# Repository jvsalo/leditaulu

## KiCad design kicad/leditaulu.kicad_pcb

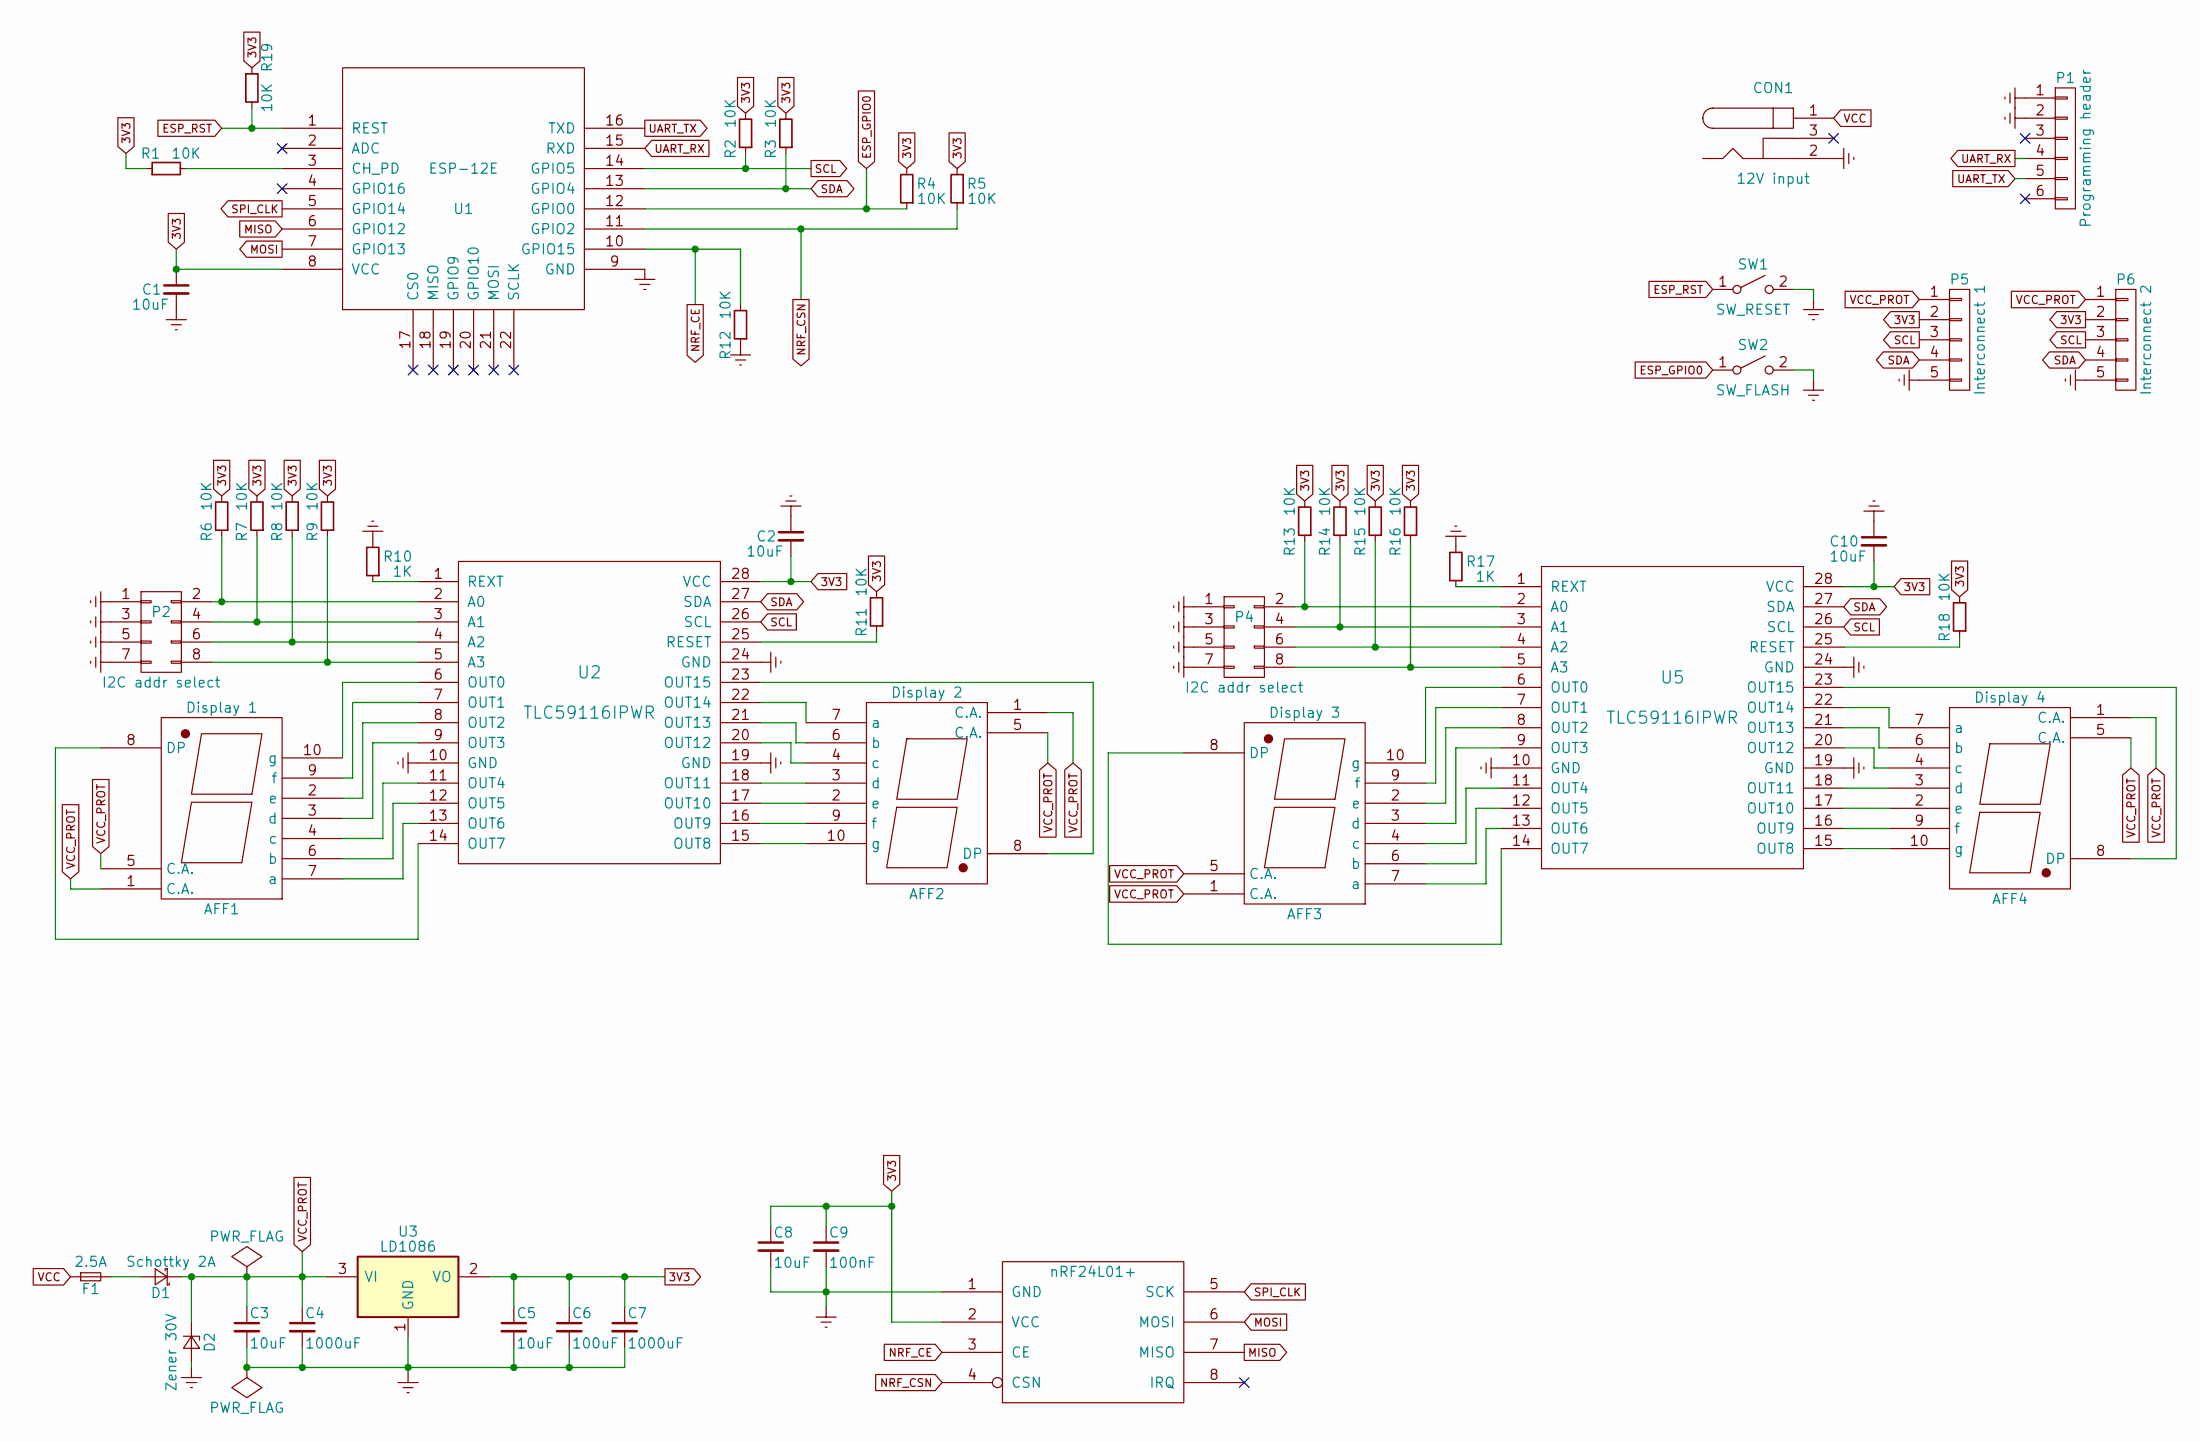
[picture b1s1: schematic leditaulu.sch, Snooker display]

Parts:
AFF1: Display 1; IDC_Header_Straight_10pins
AFF2: Display 2; IDC_Header_Straight_10pins
AFF3: Display 3; IDC_Header_Straight_10pins
AFF4: Display 4; IDC_Header_Straight_10pins
C1, C2, C3, C5, C8, C10: 10uF; C_1206_HandSoldering
C4, C7: 1000uF; CP_Radial_D10.0mm_P5.00mm
C6: 100uF; C_1206_HandSoldering
C9: 100nF; C_1206_HandSoldering
CON1: 12V input; BARREL_JACK
D1: Schottky 2A; D_SOD-123F
D2: Zener 30V; D_SMB_Handsoldering
F1: 2.5A; R_0603_HandSoldering
P1: Programming header; Pin_Header_Straight_1x06_Pitch2.54mm
P2, P4: I2C addr select; Pin_Header_Straight_2x04_Pitch2.54mm
P5: Interconnect 1; Pin_Header_Straight_1x05_Pitch2.54mm
P6: Interconnect 2; Pin_Header_Straight_1x05_Pitch2.54mm
R1, R2, R3, R4, R5, R6, R7, R8, R9, R11, R12, R13, R14, R15, R16, R18, R19: 10K; R_1206_HandSoldering
R10, R17: 1K; R_1206_HandSoldering
SW1: SW_RESET; SW_SPST_B3S-1000
SW2: SW_FLASH; SW_SPST_B3S-1000
U1: ESP-12E; ESP-12E_SMD
U2, U5: TLC59116IPWR; TSSOP-28_4.4x9.7mm_Pitch0.65mm
U3: LD1086; TO-263-3Lead
U4: nRF24L01+; NRF24L01

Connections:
3V3: C1.1, C2.2, C5.1, C6.1, C7.1, C8.1, C9.1, C10.2, P5.2, P6.2, R1.1, R2.2, R3.2, R4.2, R5.2, R6.2, R7.2, R8.2, R9.2, R11.2, R13.2, R14.2, R15.2, R16.2, R18.2, R19.1, U1.8 (VCC), U2.28 (VCC), U3.2 (VO), U4.2 (VCC), U5.28 (VCC)
ESP_GPIO0: R4.1, SW2.1 (A), U1.12 (GPIO0)
ESP_RST: R19.2, SW1.1 (A), U1.1 (REST)
Earth: C1.2, C2.1, C3.2, C4.2, C5.2, C6.2, C7.2, C8.2, C9.2, C10.1, CON1.2, D2.2 (A), P1.1, P1.2, P2.1, P2.3, P2.5, P2.7, P4.1, P4.3, P4.5, P4.7, P5.5, P6.5, R10.2, R12.1, R17.2, SW1.2 (B), SW2.2 (B), U1.9 (GND), U2.10 (GND), U2.19 (GND), U2.24 (GND), U3.1 (GND), U4.1 (GND), U5.10 (GND), U5.19 (GND), U5.24 (GND)
MISO: U1.6 (GPIO12), U4.7 (MISO)
MOSI: U1.7 (GPIO13), U4.6 (MOSI)
NRF_CE: R12.2, U1.10 (GPIO15), U4.3 (CE)
NRF_CSN: R5.1, U1.11 (GPIO2), U4.4 (CSN)
unnamed: AFF1.2 (e), U2.8 (OUT2)
unnamed: AFF1.3 (d), U2.9 (OUT3)
unnamed: AFF1.4 (c), U2.11 (OUT4)
unnamed: AFF1.6 (b), U2.12 (OUT5)
unnamed: AFF1.7 (a), U2.13 (OUT6)
unnamed: AFF1.8 (DP), U2.14 (OUT7)
unnamed: AFF1.9 (f), U2.7 (OUT1)
unnamed: AFF1.10 (g), U2.6 (OUT0)
unnamed: AFF2.2 (e), U2.17 (OUT10)
unnamed: AFF2.3 (d), U2.18 (OUT11)
unnamed: AFF2.4 (c), U2.20 (OUT12)
unnamed: AFF2.6 (b), U2.21 (OUT13)
unnamed: AFF2.7 (a), U2.22 (OUT14)
unnamed: AFF2.8 (DP), U2.23 (OUT15)
unnamed: AFF2.9 (f), U2.16 (OUT9)
unnamed: AFF2.10 (g), U2.15 (OUT8)
unnamed: AFF3.2 (e), U5.8 (OUT2)
unnamed: AFF3.3 (d), U5.9 (OUT3)
unnamed: AFF3.4 (c), U5.11 (OUT4)
unnamed: AFF3.6 (b), U5.12 (OUT5)
unnamed: AFF3.7 (a), U5.13 (OUT6)
unnamed: AFF3.8 (DP), U5.14 (OUT7)
unnamed: AFF3.9 (f), U5.7 (OUT1)
unnamed: AFF3.10 (g), U5.6 (OUT0)
unnamed: AFF4.2 (e), U5.17 (OUT10)
unnamed: AFF4.3 (d), U5.18 (OUT11)
unnamed: AFF4.4 (c), U5.20 (OUT12)
unnamed: AFF4.6 (b), U5.21 (OUT13)
unnamed: AFF4.7 (a), U5.22 (OUT14)
unnamed: AFF4.8 (DP), U5.23 (OUT15)
unnamed: AFF4.9 (f), U5.16 (OUT9)
unnamed: AFF4.10 (g), U5.15 (OUT8)
unnamed: D1.2 (A), F1.2
unnamed: P2.2, R6.1, U2.2 (A0)
unnamed: P2.4, R7.1, U2.3 (A1)
unnamed: P2.6, R8.1, U2.4 (A2)
unnamed: P2.8, R9.1, U2.5 (A3)
unnamed: P4.2, R13.1, U5.2 (A0)
unnamed: P4.4, R14.1, U5.3 (A1)
unnamed: P4.6, R15.1, U5.4 (A2)
unnamed: P4.8, R16.1, U5.5 (A3)
unnamed: R1.2, U1.3 (CH_PD)
unnamed: R10.1, U2.1 (REXT)
unnamed: R11.1, U2.25 (RESET)
unnamed: R17.1, U5.1 (REXT)
unnamed: R18.1, U5.25 (RESET)
SCL: P5.3, P6.3, R2.1, U1.14 (GPIO5), U2.26 (SCL), U5.26 (SCL)
SDA: P5.4, P6.4, R3.1, U1.13 (GPIO4), U2.27 (SDA), U5.27 (SDA)
SPI_CLK: U1.5 (GPIO14), U4.5 (SCK)
UART_RX: P1.4, U1.15 (RXD)
UART_TX: P1.5, U1.16 (TXD)
VCC: CON1.1, F1.1
VCC_PROT: AFF1.1 (C.A.), AFF1.5 (C.A.), AFF2.1 (C.A.), AFF2.5 (C.A.), AFF3.1 (C.A.), AFF3.5 (C.A.), AFF4.1 (C.A.), AFF4.5 (C.A.), C3.1, C4.1, D1.1 (K), D2.1 (K), P5.1, P6.1, U3.3 (VI)

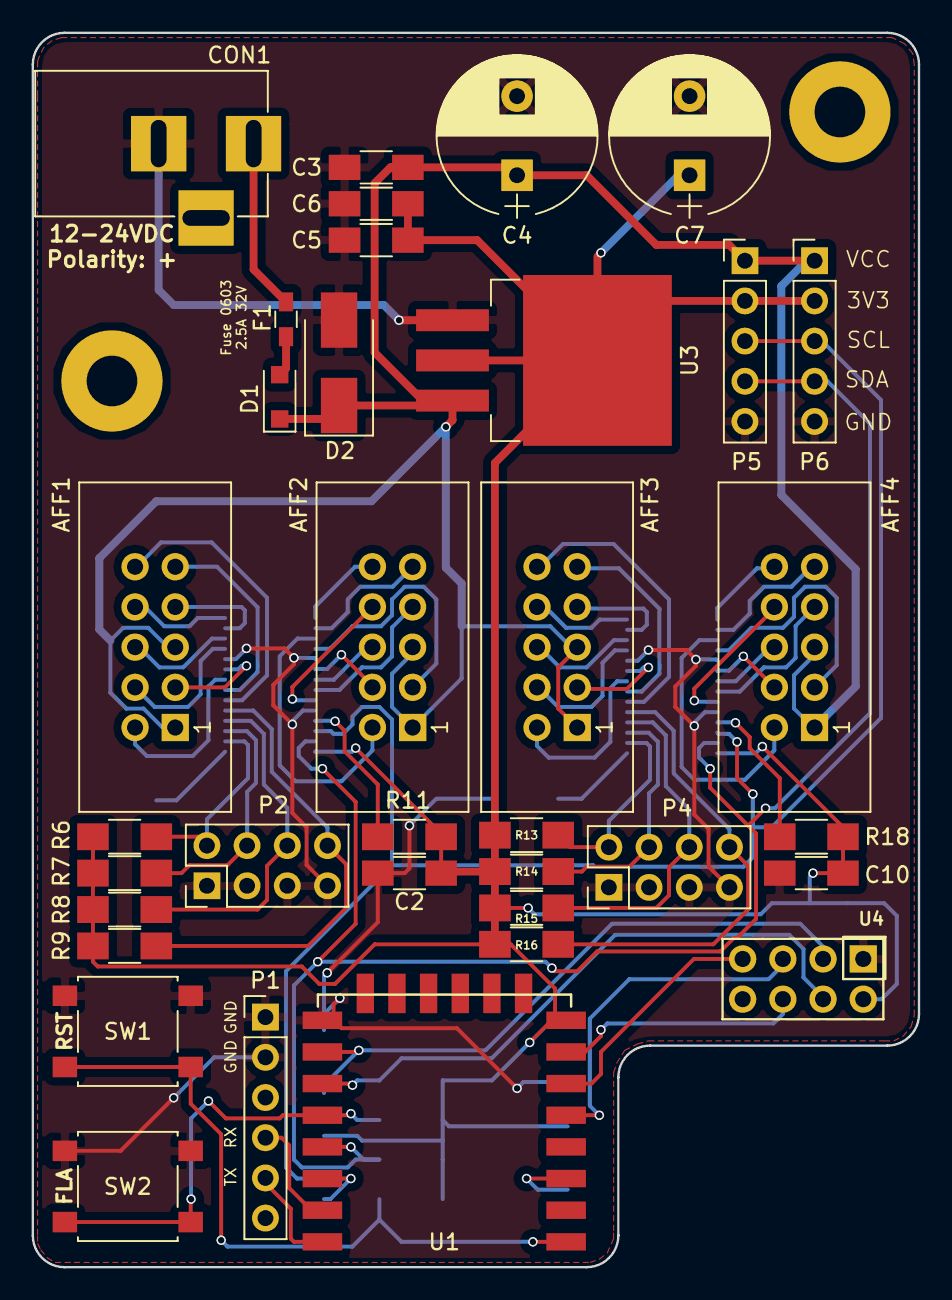
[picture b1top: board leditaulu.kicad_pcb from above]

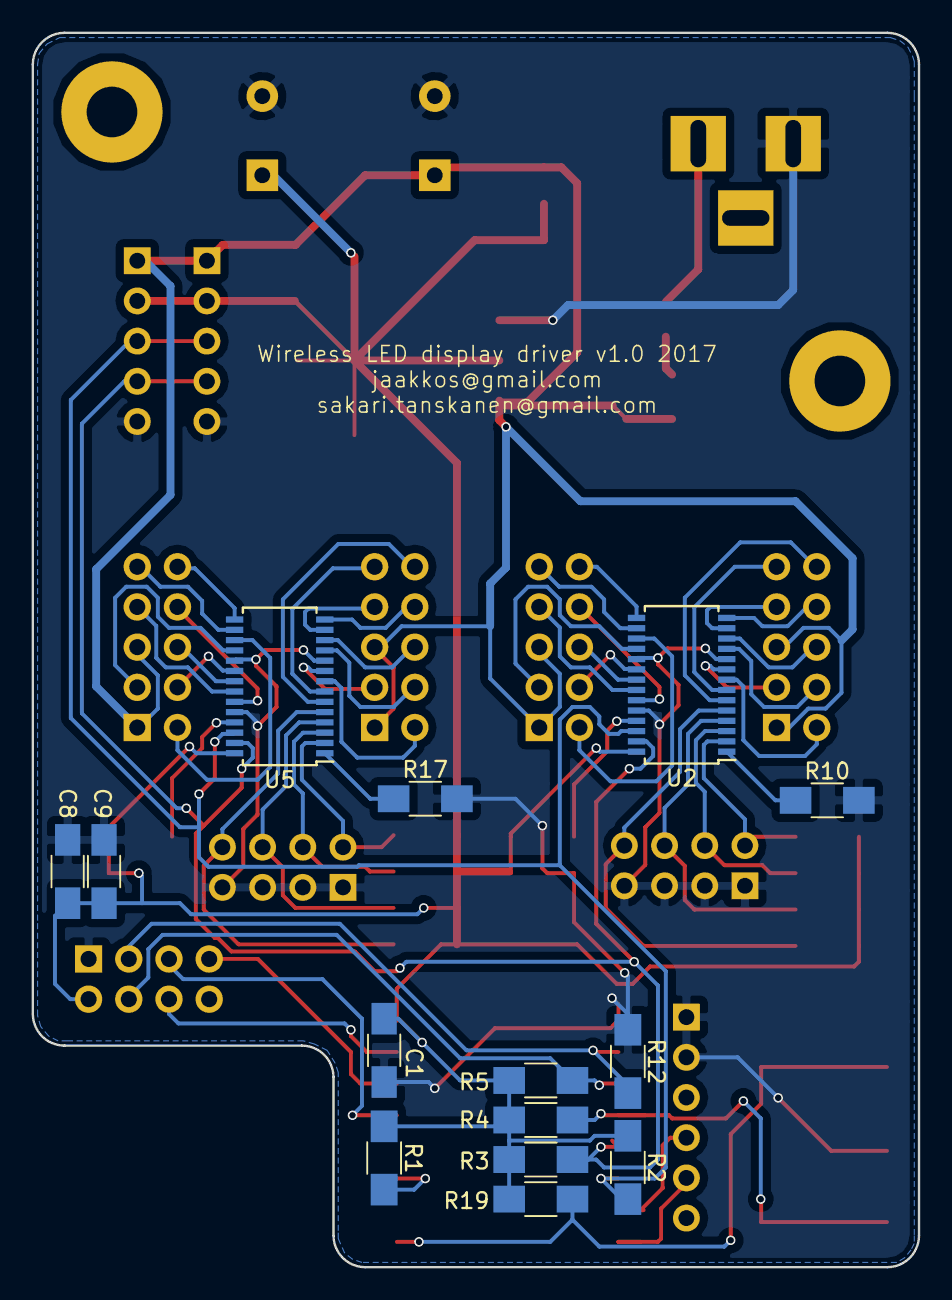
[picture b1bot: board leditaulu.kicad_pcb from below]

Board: 2 copper layers, 56.0 x 78.0 mm, 49 parts (14 on the bottom side), 61 nets.

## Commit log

2017-04-09 Initial import
2017-04-09 Started schematic; reorganize dirs
2017-04-09 Add 3V3 regulator to BOM
2017-04-09 Add regulator datasheet to BOM
2017-04-11 Continue schematic
2017-04-11 Add nRF24L01+
2017-04-26 Finish schematic and footprint associations
2017-04-27 Start routing
2017-04-27 Add buttons, continue routing
2017-04-27 Fix submodules (ESP8266)
2017-04-28 Finish routing
2017-04-29 Add power supply protection; misc. fixes
2017-05-01 Version 1.0
2017-09-11 Add remote and scoreboard code
2017-10-02 Fix issues with circular buffer
2017-10-02 Add remote/board shared constants to constants.h
2017-10-02 Remote command handling and web server
    - Modify scoreboard state with remote commands
    - Serve web page that displays current score
2017-10-02 Disable AP mode when connecting to existing wifi
2017-10-05 Update score page over websocket
2017-10-05 Add MDNS for http and ws services
2017-10-05 Testing EEPROM
2017-10-05 More serial debug
2017-10-05 Add player name setting
    - Add form for setting player names
    - Render player names based on the json sent over websocket
    - Redirect back to scoreboard after successful name submit
2017-10-05 Add form for setting wifi credentials
2017-10-05 Add FlashMem class
2017-10-05 Enable deep sleep for remote
2017-10-05 Initial FlashMem integration
2017-10-05 Fix null terminators
2017-10-05 Fix strict aliasing violation
2017-10-05 More debug
2017-10-05 Fix FlashMem
2017-10-05 Multiple improvements
